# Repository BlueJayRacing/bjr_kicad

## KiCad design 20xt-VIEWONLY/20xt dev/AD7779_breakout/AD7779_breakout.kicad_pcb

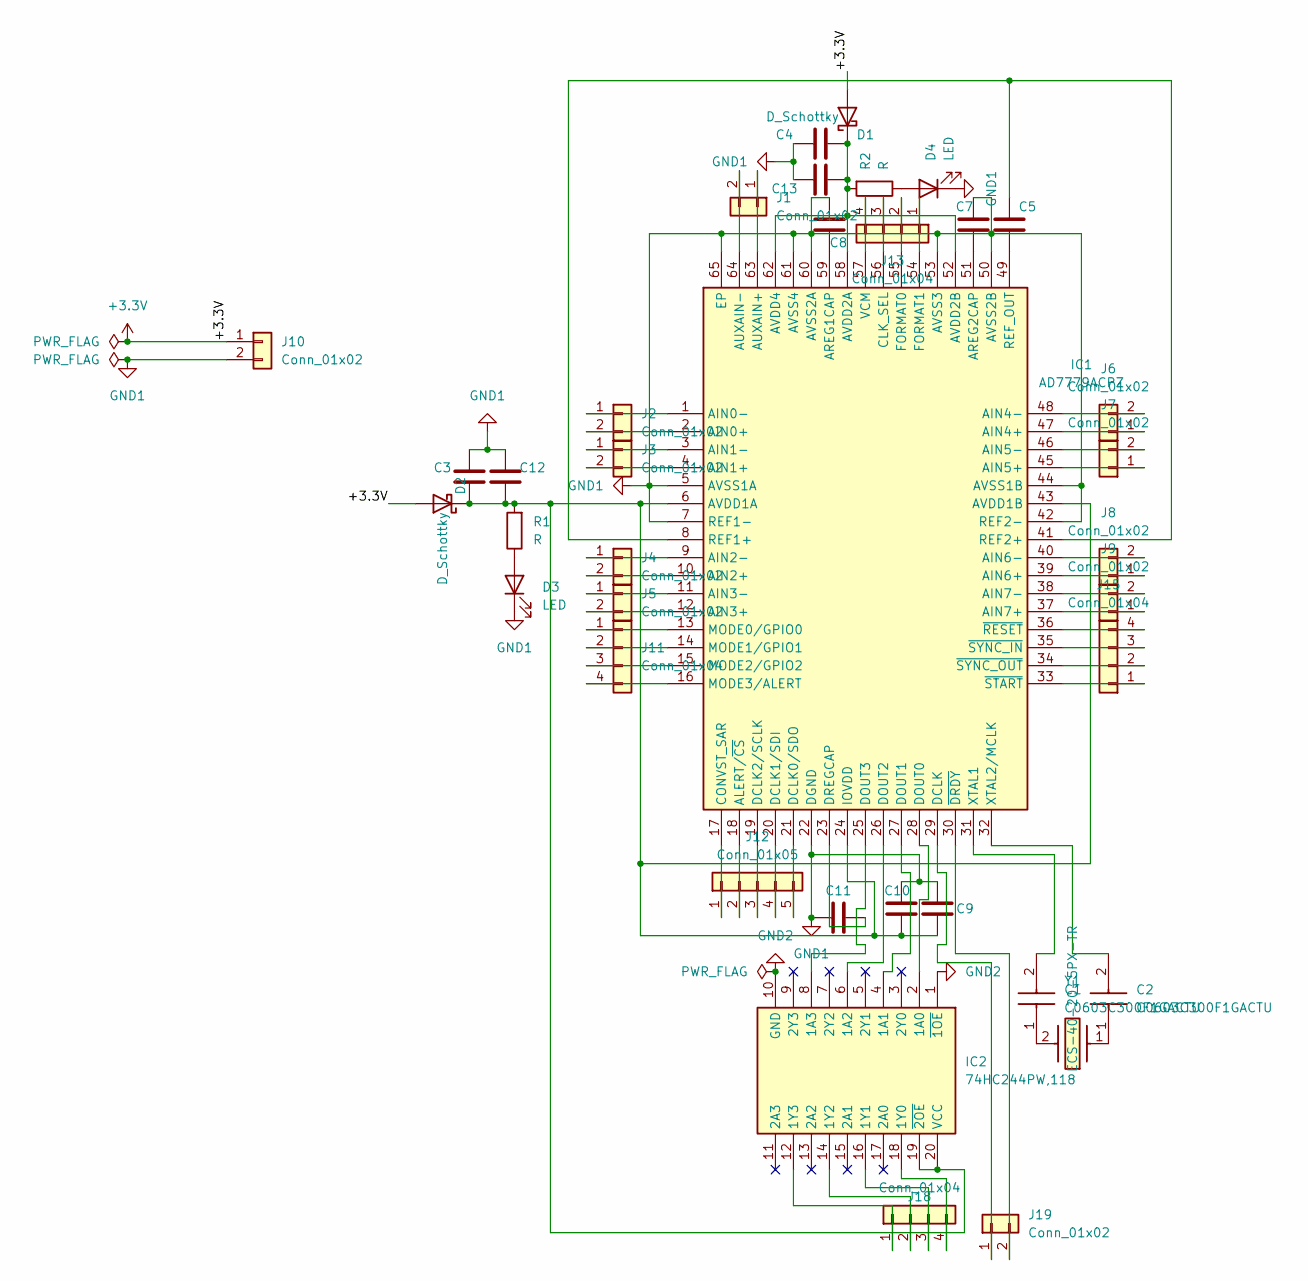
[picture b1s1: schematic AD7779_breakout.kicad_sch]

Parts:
C1, C2: C0603C300F1GACTU; C_01005_0402Metric; Mouser Part Number 80-C0603C300F1GACTU
C3, C4, C5, C9: C; CAPC1608X95N
C7, C8, C11: C; CAPC1005X55N
C10: C; C_0805_2012Metric_Pad1.18x1.45mm_HandSolder
C12: C; CAPC2012X94N
C13: C; C_0805_2012Metric
D1, D2: D_Schottky; DIOM5336X245N
D3, D4: LED; LED_0201_0603Metric
IC1: AD7779ACPZ; QFN50P900X900X80-65N-D; Mouser Part Number 584-AD7779ACPZ
IC2: 74HC244PW,118; SOP65P640X110-20N; Mouser Part Number 771-74HC244PW-T
J1, J2, J3, J4, J5, J6, J7, J8, J9, J10, J19: Conn_01x02; PinHeader_1x02_P2.54mm_Vertical
J11, J13, J15, J18: Conn_01x04; PinHeader_1x04_P2.54mm_Vertical
J12: Conn_01x05; PinHeader_1x05_P2.54mm_Vertical
R1, R2: R; R_0603_1608Metric
Y1: ECS-40-20-5PX-TR; ECS49205PXTR; Mouser Part Number 520-CSM400-20-X

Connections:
+3.3V: D1.2 (A), D2.2 (A), J10.1
GND1: C3.1, C4.1, C7.1, C8.1, C9.2, C10.2, C11.2, C12.1, C13.1, D3.1 (K), D4.1 (K), IC1.5 (AVSS1A), IC1.7 (REF1-), IC1.22 (DGND), IC1.42 (REF2-), IC1.44 (AVSS1B), IC1.50 (AVSS2B), IC1.53 (AVSS3), IC1.60 (AVSS2A), IC1.61 (AVSS4), IC1.65 (EP), J10.2
GND2: IC2.1 (~1OE), IC2.10 (GND)
unnamed: C1.1, Y1.2
unnamed: C2.1, Y1.1
unnamed: C4.2, C13.2, D1.1 (K), IC1.52 (AVDD2B), IC1.58 (AVDD2A), IC1.62 (AVDD4), R2.2
unnamed: C3.2, C9.1, C10.1, C12.2, D2.1 (K), IC1.6 (AVDD1A), IC1.24 (IOVDD), IC1.43 (AVDD1B), IC2.19 (~2OE), IC2.20 (VCC), R1.2
unnamed: D3.2 (A), R1.1
unnamed: D4.2 (A), R2.1
unnamed: IC1.2 (AIN0+), J2.2
unnamed: IC1.1 (AIN0-), J2.1
unnamed: IC1.4 (AIN1+), J3.2
unnamed: IC1.3 (AIN1-), J3.1
unnamed: IC1.10 (AIN2+), J4.2
unnamed: IC1.9 (AIN2-), J4.1
unnamed: IC1.12 (AIN3+), J5.2
unnamed: IC1.11 (AIN3-), J5.1
unnamed: IC1.47 (AIN4+), J6.1
unnamed: IC1.48 (AIN4-), J6.2
unnamed: IC1.45 (AIN5+), J7.1
unnamed: IC1.46 (AIN5-), J7.2
unnamed: IC1.39 (AIN6+), J8.1
unnamed: IC1.40 (AIN6-), J8.2
unnamed: IC1.37 (AIN7+), J9.1
unnamed: IC1.38 (AIN7-), J9.2
unnamed: IC1.18 (ALERT/~CS), J12.2
unnamed: C8.2, IC1.59 (AREG1CAP)
unnamed: C7.2, IC1.51 (AREG2CAP)
unnamed: IC1.63 (AUXAIN+), J1.1
unnamed: IC1.64 (AUXAIN-), J1.2
unnamed: IC1.56 (CLK_SEL), J13.3
unnamed: IC1.17 (CONVST_SAR), J12.1
unnamed: IC1.21 (DCLK0/SDO), J12.5
unnamed: IC1.20 (DCLK1/SDI), J12.4
unnamed: IC1.19 (DCLK2/SCLK), J12.3
unnamed: IC1.29 (DCLK), J19.1
unnamed: IC1.28 (DOUT0), IC2.2 (1A0)
unnamed: IC1.27 (DOUT1), IC2.4 (1A1)
unnamed: IC1.26 (DOUT2), IC2.6 (1A2)
unnamed: IC1.25 (DOUT3), IC2.8 (1A3)
unnamed: C11.1, IC1.23 (DREGCAP)
unnamed: IC1.55 (FORMAT0), J13.2
unnamed: IC1.54 (FORMAT1), J13.1
unnamed: IC1.13 (MODE0/GPIO0), J11.1
unnamed: IC1.14 (MODE1/GPIO1), J11.2
unnamed: IC1.15 (MODE2/GPIO2), J11.3
unnamed: IC1.16 (MODE3/ALERT), J11.4
unnamed: C5.1, IC1.8 (REF1+), IC1.41 (REF2+)
unnamed: C5.2, IC1.49 (REF_OUT)
unnamed: IC1.57 (VCM), J13.4
unnamed: C1.2, IC1.31 (XTAL1)
unnamed: C2.2, IC1.32 (XTAL2/MCLK)
unnamed: IC1.30 (~DRDY), J19.2
unnamed: IC1.36 (~RESET), J15.4
unnamed: IC1.33 (~START), J15.1
unnamed: IC1.35 (~SYNC_IN), J15.3
unnamed: IC1.34 (~SYNC_OUT), J15.2
unnamed: IC2.18 (1Y0), J18.4
unnamed: IC2.16 (1Y1), J18.3
unnamed: IC2.14 (1Y2), J18.2
unnamed: IC2.12 (1Y3), J18.1

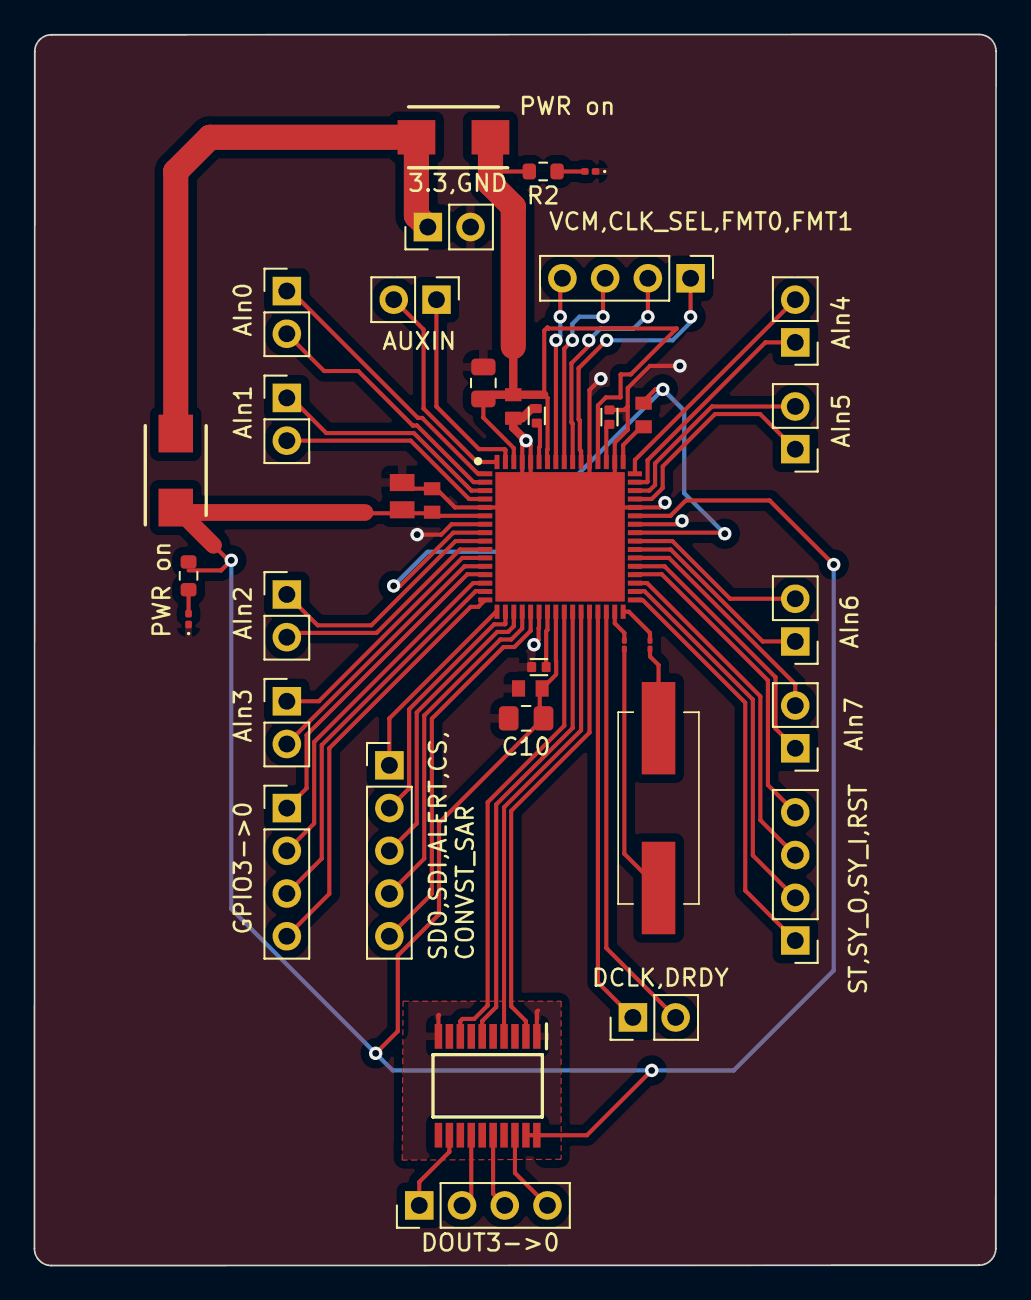
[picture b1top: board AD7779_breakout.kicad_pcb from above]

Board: 2 copper layers, 57.2 x 73.2 mm, 37 parts (0 on the bottom side), 61 nets.

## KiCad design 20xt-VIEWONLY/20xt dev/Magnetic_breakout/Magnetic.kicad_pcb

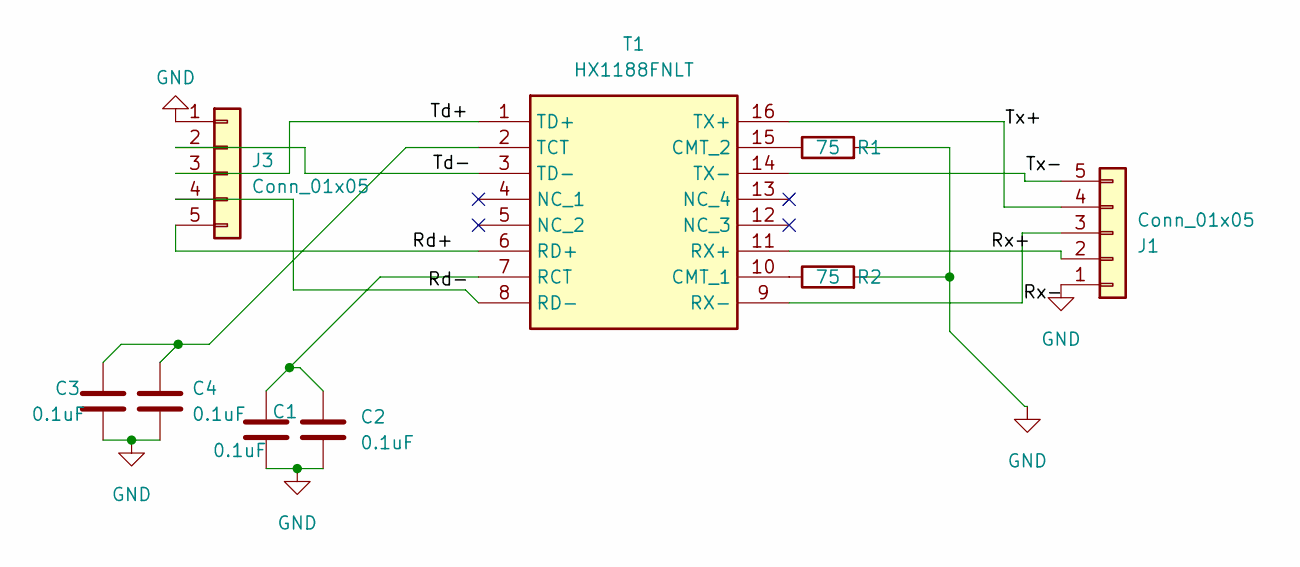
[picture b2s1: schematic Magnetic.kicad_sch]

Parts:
C1, C2, C3, C4: 0.1uF; C_0603_1608Metric
J1, J3: Conn_01x05; Molex_PicoBlade_53047-0510_1x05_P1.25mm_Vertical
R1, R2: 75; R_0603_1608Metric
T1: HX1188FNLT; Mouser Part Number 673-HX1188FNLT

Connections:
/Rd+: J3.5, T1.6 (RD+)
/Rd-: J3.4, T1.8 (RD-)
/Rx+: J1.2, T1.11 (RX+)
/Rx-: J1.3, T1.9 (RX-)
/Td+: J3.3, T1.1 (TD+)
/Td-: J3.2, T1.3 (TD-)
/Tx+: J1.4, T1.16 (TX+)
/Tx-: J1.5, T1.14 (TX-)
GND: C1.2, C2.2, C3.2, C4.2, J1.1, J3.1, R1.2, R2.2
unnamed: R2.1, T1.10 (CMT_1)
unnamed: R1.1, T1.15 (CMT_2)
unnamed: C1.1, C2.1, T1.7 (RCT)
unnamed: C3.1, C4.1, T1.2 (TCT)

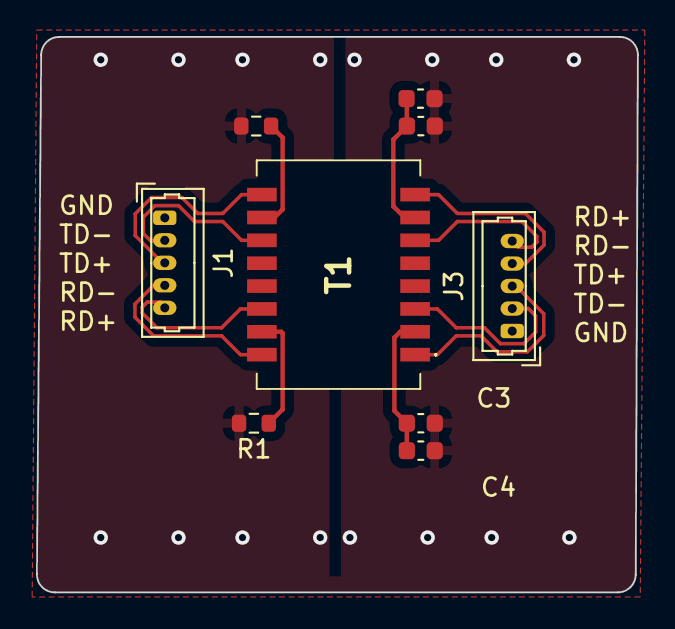
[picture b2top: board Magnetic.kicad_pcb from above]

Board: 2 copper layers, 33.4 x 30.9 mm, 9 parts (0 on the bottom side), 13 nets.

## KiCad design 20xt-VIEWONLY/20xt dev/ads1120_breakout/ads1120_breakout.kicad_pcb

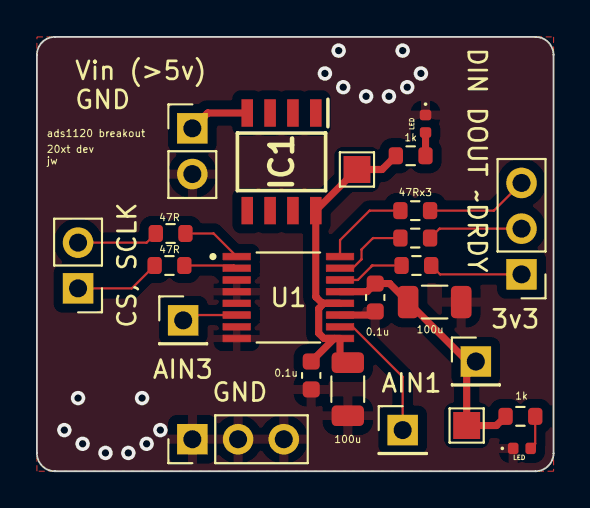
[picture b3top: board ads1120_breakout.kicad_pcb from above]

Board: 2 copper layers, 28.7 x 24.1 mm, 24 parts (0 on the bottom side), 18 nets.

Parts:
C1, C4: 100u; C_1206_3216Metric
C2, C3: 0.1u; C_0603_1608Metric
D1, D2: LED; D_0402_1005Metric
IC1: LT1009S8#PBF; SOIC127P599X175-8N
J1, J2: Conn_01x02; PinHeader_1x02_P2.54mm_Vertical
J3, J4, J6: Conn_01x01; PinHeader_1x01_P2.54mm_Vertical
J5, J7: Conn_01x03; PinHeader_1x03_P2.54mm_Vertical
R1, R2, R3, R4, R5: 47; R_0603_1608Metric
R6, R7: 1k; R_0603_1608Metric
TP1, TP2: TestPoint; TestPoint_Pad_1.5x1.5mm
U1: ADS1120IPWR; SOP65P640X120-16N

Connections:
2.5v: C1.1, C2.2, IC1.8 ((+)_2), R7.1, TP2.1, U1.9 (REFP0), U1.12 (AVDD)
3v3: C3.2, C4.1, J6.1, R6.1, TP1.1, U1.13 (DVDD)
DIN: J5.3, R2.1
GND: C1.2, C2.1, C3.1, C4.2, D1.1 (K), D2.1 (K), J2.2, J7.1, J7.2, J7.3, U1.3 (CLK), U1.4 (DGND), U1.5 (AVSS), U1.7 (AIN2), U1.8 (REFN0), U1.11 (AIN0/REFP1)
unnamed: D1.2 (A), R6.2
unnamed: D2.2 (A), R7.2
unnamed: J1.1, R1.1
unnamed: J1.2, R3.1
unnamed: J3.1, U1.10 (AIN1)
unnamed: J4.1, U1.6 (AIN3/REFN1)
unnamed: J5.1, R4.1
unnamed: J5.2, R5.2
unnamed: R2.2, U1.16 (DIN)
unnamed: R5.1, U1.15 (DOUT/~DRDY)
unnamed: R3.2, U1.1 (SCLK)
unnamed: R1.2, U1.2 (~CS)
unnamed: R4.2, U1.14 (~DRDY)
Vin: IC1.4 ((-)), J2.1

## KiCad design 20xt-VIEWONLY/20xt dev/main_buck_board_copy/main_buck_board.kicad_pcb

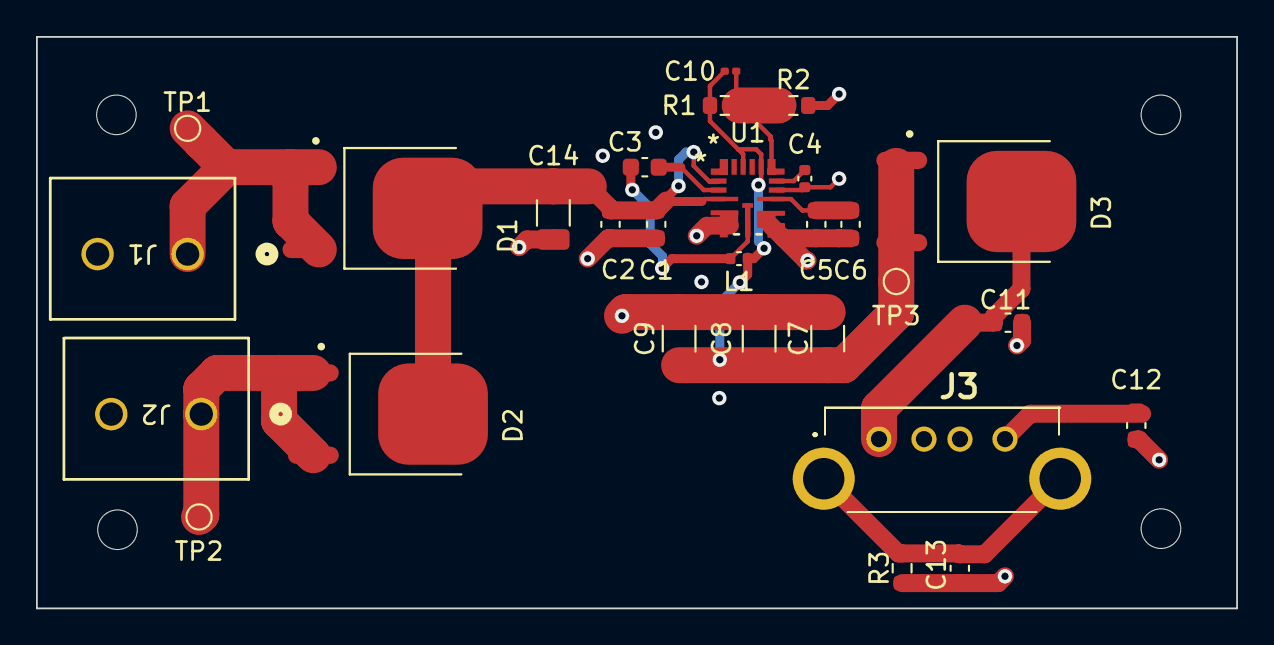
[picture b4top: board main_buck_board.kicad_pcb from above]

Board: 4 copper layers, 66.7 x 31.8 mm, 32 parts (0 on the bottom side), 13 nets.

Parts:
C1, C3, C5, C11, C12, C13: 0.1uF; C_0603_1608Metric
C2, C6: 10uF; C_0603_1608Metric
C4: 2.2uF; C_0402_1005Metric
C7, C8, C9, C14: 100uF; C_1206_3216Metric
C10: 56pF; C_0201_0603Metric
D1, D2, D3: D_Schottky_AKA; DPAK228P990X239-4N
H1, H2, H3, H4: MountingHole; MountingHole_2.2mm_M2
J1, J2: 691137710002; CONN2_710002_WRE
J3: UJ2-AV-4-TH; UJ2AV4TH
L1: 2.2uH; C_0402_1005Metric
R1: 51.1k; R_0603_1608Metric
R2: 10k; R_0603_1608Metric
R3: 100k; R_0603_1608Metric
TP1, TP2, TP3: TestPoint; TestPoint_Pad_D1.0mm
U1: 21-100700_90-100240_ADI

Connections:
GND: C1.2, C2.2, C4.2, C5.2, C6.2, C7.1, C8.1, C9.1, C11.2, C12.1, C13.2, C14.2, J1.2, J2.2, R2.2, R3.2, U1.4 (PGND), U1.5 (PGND), U1.7 (PGND), U1.8 (PGND), U1.10 (GND)
unnamed: C5.1, C6.1, U1.9 (SUP)
unnamed: C12.2, J3.4
unnamed: C13.1, J3.MH1, J3.MH2, R3.1
unnamed: D1.1 (A), D1.3 (A), J1.1, TP1.1
unnamed: C1.1, C2.1, C14.1, D1.2 (K), D2.2 (K), U1.1 (EN), U1.3 (SUP)
unnamed: D2.1 (A), D2.3 (A), J2.1, TP2.1
unnamed: C11.1, D3.2 (K), J3.1
unnamed: C4.1, U1.11 (BIAS)
unnamed: C3.1, U1.2 (BST)
unnamed: C10.2, R1.2, R2.1, U1.12 (FB)
unnamed: C3.2, L1.1, U1.6 (LX)
unnamed: C7.2, C8.2, C9.2, C10.1, D3.1 (A), D3.3 (A), L1.2, R1.1, TP3.1, U1.13 (OUT), U1.15 (PGOOD)

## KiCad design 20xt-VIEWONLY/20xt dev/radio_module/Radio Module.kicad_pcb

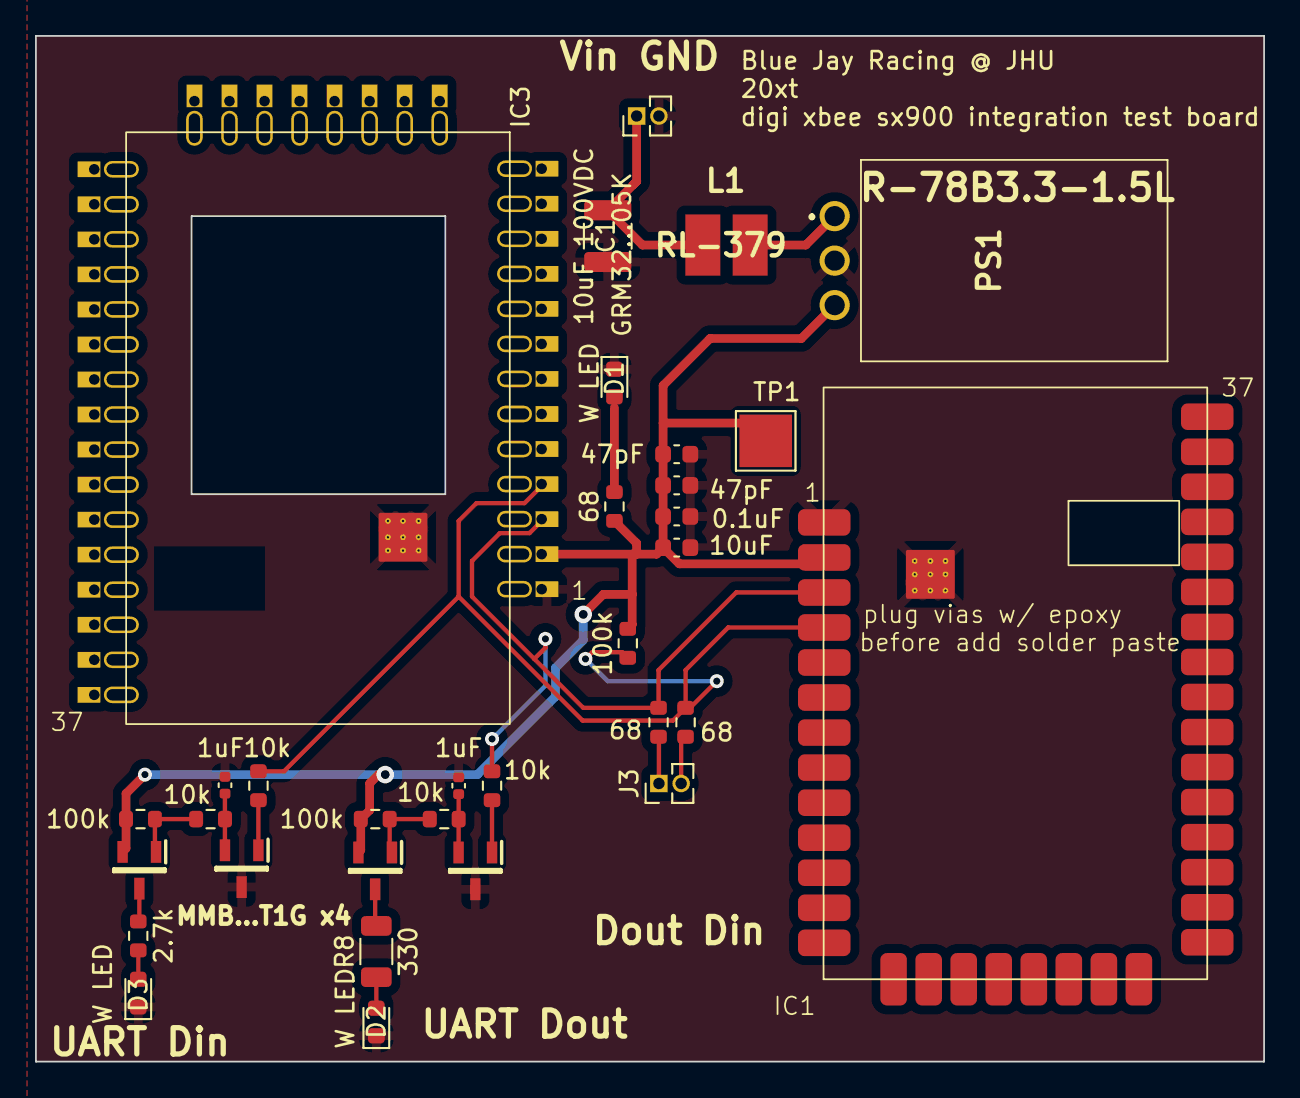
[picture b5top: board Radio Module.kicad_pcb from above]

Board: 2 copper layers, 70.1 x 58.5 mm, 33 parts (0 on the bottom side), 19 nets.

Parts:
C1: 10uF 100VDC; C_1210_3225Metric
C2: 10uF; C_0603_1608Metric
C3: 0.1uF; C_0603_1608Metric
C4, C5: 47pF; C_0603_1608Metric
C6, C7: 1uF; C_0402_1005Metric
D1, D3: W LED; LED_0603_1608Metric
D2: LED; LED_0603_1608Metric
IC1: XBP9X-DMUS-011; xbee sx 900
IC3: XBP9X-DMUS-011; xbee sx 900 flexy
IC4, IC5, IC6, IC7: MMBT3906LT1G; SOT96P237X111-3N
J3, J4: Conn_01x02; PinHeader_1x02_P1.27mm_Vertical
L1: 3.9uH; RLS397
PS1: R-78B3.3-1.5L; R78B5015L
R1, R2, R3: 68; R_0603_1608Metric
R4, R7, R11: 100k; R_0603_1608Metric
R5, R6, R9, R10: 10k; R_0603_1608Metric
R8: 330; R_1206_3216Metric
R12: 2.7k; R_0603_1608Metric
TP1: TestPoint; TestPoint_Pad_3.0x3.0mm

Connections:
Din: IC1.4 (DIN/DIO14/~CONFIG), IC3.4 (DIN/DIO14/~CONFIG), R1.2, R4.2, R10.1
Dout: IC1.3 (DIO13/DOUT), IC3.3 (DIO13/DOUT), R2.2, R5.1
GND: C1.2, C2.1, C3.1, C4.1, C5.1, C6.2, C7.2, D1.1 (K), D2.1 (K), D3.1 (K), IC1.1 (GND_1), IC1.38 (GND_6), IC3.1 (GND_1), IC3.38 (GND_6), IC4.3 (C), IC6.3 (C), J4.2, PS1.2 (GND)
unnamed: D1.2 (A), R3.1
unnamed: D2.2 (A), R8.1
unnamed: D3.2 (A), R12.1
unnamed: IC4.1 (B), R5.2
unnamed: C6.1, IC4.2 (E), R6.1
unnamed: IC5.1 (B), R6.2, R7.2
unnamed: IC5.3 (C), R8.2
unnamed: IC6.1 (B), R10.2
unnamed: C7.1, IC6.2 (E), R9.1
unnamed: IC7.1 (B), R9.2, R11.2
unnamed: IC7.3 (C), R12.2
unnamed: J3.1, R2.1
unnamed: J3.2, R1.1
unnamed: L1.2, PS1.1 (+VIN)
Vcc: C2.2, C3.2, C4.2, C5.2, IC1.2 (VCC), IC3.2 (VCC), IC5.2 (E), IC7.2 (E), PS1.3 (+VOUT), R3.2, R4.1, R7.1, R11.1, TP1.1
Vin: C1.1, J4.1, L1.1

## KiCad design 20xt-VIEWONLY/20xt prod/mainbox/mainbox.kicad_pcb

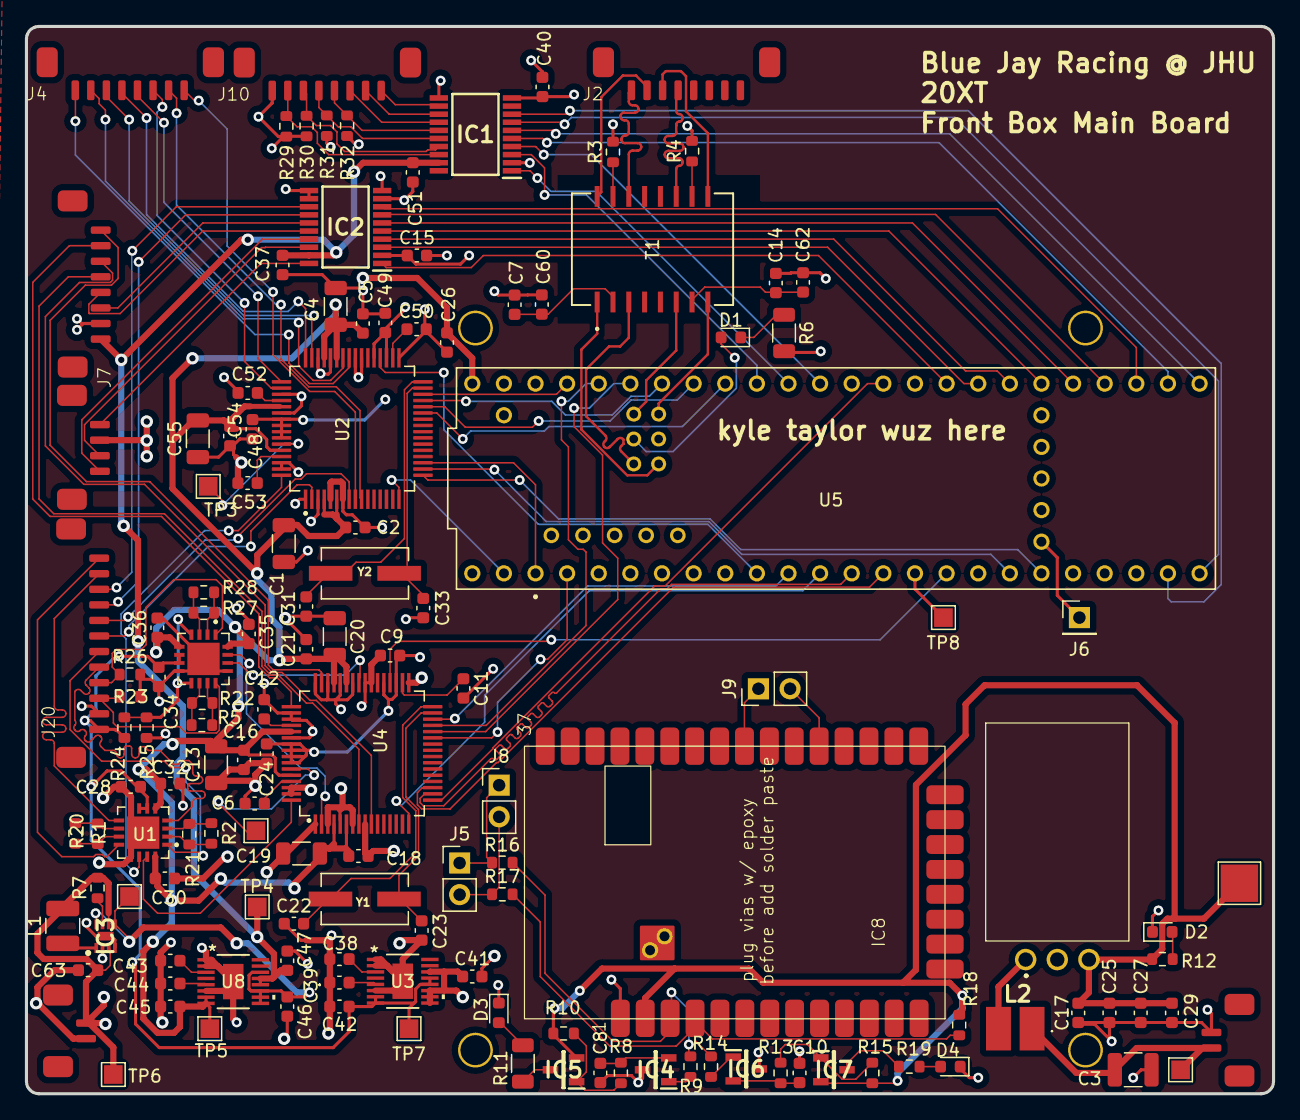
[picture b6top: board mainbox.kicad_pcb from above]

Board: 4 copper layers, 100.2 x 85.7 mm, 141 parts (0 on the bottom side), 139 nets.

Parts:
C1, C4, C13, C19, C20, C55: 100uF; C_1206_3216Metric
C2, C5, C9, C15, C16, C18, C21, C24, C25, C26, C28, C30, C32, C34, C35, C36, C37, C39, C40, C41, C44, C46, C48, C49, C51, C54, C60, C62: 0.1uF; C_0603_1608Metric
C3: 10uF 100VDC; C_1210_3225Metric
C6, C7, C8, C10, C11, C12, C14, C38, C42, C43, C45, C47, C50, C52, C53: 1uF; C_0603_1608Metric
C17: 10uF; C_0603_1608Metric
C22, C23, C31, C33: 35pF; C_0603_1608Metric
C27, C29: 47pF; C_0603_1608Metric
C63: 4.7uF; C_0603_1608Metric
D1, D2, D3, D4: LED; LED_0603_1608Metric
H1, H2, H3, H4: MountingHole; 2.35mm_mounting_hole
IC1, IC2: TXB0108PWR; SOP65P640X120-20N
IC3: MIC2876-5.5YMT-TR; SON50P200X200X60-9N-D
IC4, IC5, IC6, IC7: MMBT3906LT1G; SOT96P237X111-3N
IC8: XBP9X-DMUS-011; xbee sx 900
J1: Conn_01x04; SMD_picoblade_hori_1x04
J2, J4, J7, J10: Conn_01x08; SMD_picoblade_hori_1x08
J3, J21: Conn_01x02; SMD_picoblade_hori_1x02
J5, J8, J9: Conn_01x02; PinHeader_1x02_P2.54mm_Vertical
J6: Conn_01x01; PinHeader_1x01_P2.54mm_Vertical
J20: Conn_01x12; SMD_picoblade_hori_1x12
L1: 1uH; L_1210_3225Metric
L2: 3.9uH; RLS397
PS1: R-78B3.3-1.5L; R78B5015L
R1, R2, R5, R20, R21, R22, R27, R28: 47; R_0603_1608Metric
R3, R4: 75; R_0603_1608Metric
R6, R11: 330; R_1206_3216Metric
R7: 1M; R_0603_1608Metric
R8, R9, R13, R14: 10k; R_0603_1608Metric
R10, R15, R18, R29, R30, R31, R32: 100k; R_0603_1608Metric
R12, R16, R17: 68; R_0603_1608Metric
R19: 2.7k; R_0603_1608Metric
R23, R24, R25, R26: 120; R_0603_1608Metric
T1: 2337822-1; CONN16_2337822-1_TEC
TP1, TP2, TP3, TP4, TP5, TP6, TP7, TP8, TP10: TestPoint; TestPoint_Pad_1.5x1.5mm
TP9: TestPoint; TestPoint_Pad_3.0x3.0mm
U1, U6: AD8222ACPZ-R7; QFN65P400X400X80-17N
U2, U4: AD7768BSTZ; QFP50P1200X1200X160-64N
U3: LT6658AHMSE-2.5-PBF; MSE_16_ADI
U5: DEV-16771; MODULE_DEV-16771
U8: LT6658AHMSE-5-PBF; MSE_16_ADI
Y1, Y2: ECS-160-20-3X-TR; XTAL_ECS-160-20-3X-TR

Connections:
2.5vsg: C28.1, C34.1, C42.1, J20.12, R24.1, TP7.1, U1.6 (REF1), U1.7 (REF2), U3.7 (VOUT2_S), U3.8 (VOUT2_F), U3.12 (VOUT1_F), U3.13 (VOUT1_S), U6.6 (REF1), U6.7 (REF2)
3v3: C9.1, C15.1, C24.1, C40.1, C48.1, C49.1, IC1.2 (VCCA), IC1.10 (OE), IC2.2 (VCCA), IC2.10 (OE), TP8.1, U2.35 (IOVDD), U2.37 (~START), U2.55 (FORMAT1), U2.56 (FORMAT0), U2.57 (~PIN/SPI), U2.58 (CLK_SEL), U4.35 (IOVDD), U4.37 (~START), U4.55 (FORMAT1), U4.56 (FORMAT0), U4.57 (~PIN/SPI), U4.58 (CLK_SEL), U5.3.3V_1 (3.3V)
5.2v: C46.1, IC3.5 (OUTS), IC3.8 (OUT), TP2.1, U8.9 (*OD), U8.10 (VIN2), U8.11 (VIN1), U8.14 (VIN)
5vadc: C1.2, C2.1, C4.2, C5.1, C13.2, C16.1, C18.1, C19.2, C20.2, C21.1, C30.1, C32.1, C35.1, C36.1, C45.1, C54.1, C55.2, TP5.1, U1.5 (+VS), U1.16 (+VS__1), U2.4 (AVDD1A), U2.6 (REF1+), U2.43 (REF2+), U2.45 (AVDD1B), U2.53 (AVDD2B), U2.60 (AVDD2A), U4.4 (AVDD1A), U4.6 (REF1+), U4.43 (REF2+), U4.45 (AVDD1B), U4.53 (AVDD2B), U4.60 (AVDD2A), U6.5 (+VS), U6.16 (+VS__1), U8.7 (VOUT2_S), U8.8 (VOUT2_F)
5vanalog: C37.1, C47.1, C51.1, IC1.19 (VCCB), IC2.19 (VCCB), J7.8, TP4.1, U8.12 (VOUT1_F), U8.13 (VOUT1_S)
5vin: C26.1, C41.1, C63.2, IC3.3 (IN), IC3.6 (EN), J1.2, J21.1, L1.2, R7.2, TP6.1, U3.9 (*OD), U3.10 (VIN2), U3.11 (VIN1), U3.14 (VIN), U5.VIN
5vradio: C3.1, J3.1, L2.1, TP10.1
!CS1: U4.16 (ST0/~CS), U5.10 (CS1)
!CS2: U2.16 (ST0/~CS), U5.0 (RX1)
/teensy/Rx+: J2.5, T1.11 (RX+)
/teensy/Rx-: J2.6, T1.9 (RX-)
/teensy/Tx+: J2.7, T1.16 (TX+)
/teensy/Tx-: J2.8, T1.14 (TX-)
Din: IC8.4 (DIN/DIO14/~CONFIG), R14.1, R17.2, R18.2
Dout: IC8.3 (DIO13/DOUT), R9.1, R16.2
GND: C1.1, C2.2, C3.2, C4.1, C5.2, C6.2, C7.1, C8.2, C9.2, C10.2, C11.2, C12.2, C13.1, C14.1, C15.2, C16.2, C17.1, C18.2, C19.1, C20.1, C21.2, C22.1, C23.1, C24.2, C25.1, C26.2, C27.1, C28.2, C29.1, C30.2, C31.1, C32.2, C33.1, C34.2, C35.2, C36.2, C37.2, C38.2, C39.2, C40.2, C41.2, C42.2, C43.2, C44.2, C45.2, C46.2, C47.2, C48.2, C49.2, C50.2, C51.2, C52.2, C53.2, C54.2, C55.1, C60.2, C62.2, C63.1, D2.1 (K), D3.1 (K), D4.1 (K), IC1.11 (GND), IC2.9 (A8), IC2.11 (GND), IC2.12 (B8), IC3.2 (PGND), IC3.4 (AGND), IC3.9 (EP), IC4.3 (C), IC6.3 (C), IC8.1 (GND_1), IC8.38 (GND_6), J3.2, J7.7, J10.8, J20.11, J21.2, PS1.2 (GND), R3.2, R4.2, R6.2, R23.2, R25.2, R26.2, R29.1, R30.1, R31.1, R32.1, U1.8 (-VS__1), U1.13 (-VS), U1.17 (EP), U2.1 (AIN1-), U2.3 (AVSS1A), U2.5 (REF1-), U2.7 (AIN2-), U2.33 (DGND), U2.39 (AIN7+), U2.40 (AIN7-), U2.44 (REF2-), U2.46 (AVSS1B), U2.51 (AVSS2B), U2.54 (AVSS), U2.62 (AVSS2A), U2.63 (AIN0-), U3.1 (GND), U3.2 (GND), U3.6 (GND), U3.EPAD, U4.1 (AIN1-), U4.3 (AVSS1A), U4.5 (REF1-), U4.7 (AIN2-), U4.9 (AIN3-), U4.33 (DGND), U4.39 (AIN7+), U4.40 (AIN7-), U4.42 (AIN6-), U4.44 (REF2-), U4.46 (AVSS1B), U4.48 (AIN5-), U4.50 (AIN4-), U4.51 (AVSS2B), U4.54 (AVSS), U4.62 (AVSS2A), U4.63 (AIN0-), U5.GND1 (GND), U5.GND2 (GND__1), U5.GND3 (GND__2), U5.GND4 (GND__3), U5.GND5 (GND__4), U5.USB_GND1 (USB_GND), U5.USB_GND2 (USB_GND__1), U6.8 (-VS__1), U6.13 (-VS), U6.17 (EP), U8.1 (GND), U8.2 (GND), U8.6 (GND), U8.EPAD
unnamed: D1.2 (A), U5.LED
unnamed: D1.1 (K), R6.1
unnamed: D2.2 (A), R12.1
unnamed: D3.2 (A), R11.1
unnamed: D4.2 (A), R19.1
unnamed: IC2.1 (A1), U5.41 (A17)
unnamed: IC2.3 (A2), U5.40 (A16)
unnamed: IC2.4 (A3), U5.39 (A15)
unnamed: IC2.5 (A4), U5.38 (A14)
unnamed: IC2.6 (A5), U5.37 (CS3)
unnamed: IC2.7 (A6), U5.36 (CS2)
unnamed: IC2.8 (A7), U5.35 (TX8)
unnamed: IC3.1 (SW), L1.1
unnamed: IC3.7 (/PG), R7.1
unnamed: IC4.1 (B), R9.2
unnamed: C8.1, IC4.2 (E), R8.1
unnamed: IC5.1 (B), R8.2, R10.2
unnamed: IC5.3 (C), R11.2
unnamed: IC6.1 (B), R14.2
unnamed: C10.1, IC6.2 (E), R13.1
unnamed: IC7.1 (B), R13.2, R15.2
unnamed: IC7.3 (C), R19.2
unnamed: IC8.29 (DIO6/~RTS), J9.1
unnamed: IC8.26 (DIO9/ON/~SLEEP), J9.2
unnamed: J4.1, U2.9 (AIN3-)
unnamed: J4.2, U2.10 (AIN3+)
unnamed: J4.3, U2.50 (AIN4-)
unnamed: J4.4, U2.49 (AIN4+)
unnamed: J4.5, U2.48 (AIN5-)
unnamed: J4.6, U2.47 (AIN5+)
unnamed: J4.7, U2.42 (AIN6-)
unnamed: J4.8, U2.41 (AIN6+)
unnamed: J5.1, J8.1, R16.1
unnamed: J5.2, J8.2, R17.1
unnamed: J6.1, U5.VBAT
unnamed: J20.1, U1.12 (-IN2)
unnamed: J20.2, U1.9 (+IN2)
unnamed: J20.7, U1.1 (-IN1)
unnamed: J20.8, U1.4 (+IN1)
unnamed: L2.2, PS1.1 (+VIN)
unnamed: R4.1, T1.10 (CMT_1)
unnamed: R3.1, T1.15 (CMT_2)
unnamed: C14.2, C62.1, T1.7 (RCT)
unnamed: C7.2, C60.1, T1.2 (TCT)
unnamed: R2.1, R21.1, U1.2 (RG1)
unnamed: R2.2, R21.2, U1.3 (RG1__1)
unnamed: R1.1, R20.1, U1.10 (RG2)
unnamed: R1.2, R20.2, U1.11 (RG2__1)
unnamed: C50.1, U2.34 (DREGCAP)
unnamed: C53.1, U2.61 (REGCAPA)
unnamed: C52.1, U2.52 (REGCAPB)
unnamed: TP3.1, U2.59 (VCM)
unnamed: C38.1, U3.3 (BYPASS)
unnamed: C39.1, U3.5 (NR)
unnamed: C11.1, U4.34 (DREGCAP)
unnamed: C6.1, U4.61 (REGCAPA)
unnamed: C12.1, U4.52 (REGCAPB)
unnamed: TP1.1, U4.59 (VCM)
unnamed: R27.1, R28.1, U6.2 (RG1)
unnamed: R27.2, R28.2, U6.3 (RG1__1)
unnamed: R5.1, R22.1, U6.10 (RG2)
unnamed: R5.2, R22.2, U6.11 (RG2__1)
unnamed: C43.1, U8.3 (BYPASS)
unnamed: C44.1, U8.5 (NR)
Rd+: T1.6 (RD+), U5.R+
Rd-: T1.8 (RD-), U5.R-
S1: IC1.5 (A4), U5.34 (RX8)
S2: IC1.6 (A5), U5.33 (MCLK2)
S3: IC1.7 (A6), U5.32 (OUT1B)
S4: IC1.8 (A7), U5.31 (CTX3)
S15: IC1.15 (B5), J10.4, R32.2
S25: IC1.16 (B4), J10.5, R31.2
S35: IC1.17 (B3), J10.6, R30.2
S45: IC1.18 (B2), J10.7, R29.2
SCL: IC1.3 (A2), U5.17 (A3)
SCL5: IC1.14 (B6), J10.3
SCLK1: U4.17 (ST1/SCLK), U5.13 (SCK)
SCLK2: U2.17 (ST1/SCLK), U5.27 (A13)
SDA: IC1.1 (A1), U5.16 (A2)
SDA5: IC1.13 (B7), J10.2
SDI1: U4.18 (DEC1/SDI), U5.11 (MOSI)
SDI2: U2.18 (DEC1/SDI), U5.26 (A12)
SDO1: U4.19 (DEC0/SDO), U5.12 (MISO)
SDO2: U2.19 (DEC0/SDO), U5.1 (TX1)
Td+: T1.1 (TD+), U5.T+
Td-: T1.3 (TD-), U5.T-
Vcc: C17.2, C25.2, C27.2, C29.2, IC5.2 (E), IC7.2 (E), IC8.2 (VCC), PS1.3 (+VOUT), R10.1, R12.2, R15.1, R18.1, TP9.1
aux1.1: J20.6, U2.2 (AIN1+)
aux1.2: J20.5, U2.8 (AIN2+)
auxsg: U1.14 (OUT2), U2.64 (AIN0+)
brake1: J7.2, U4.49 (AIN4+)
brake2: J7.1, U4.47 (AIN5+)
daux1: IC2.14 (B6), J20.4
daux2: IC2.13 (B7), J20.3
dclk1: U4.28 (DCLK), U5.21 (A7)
dclk2: U2.28 (DCLK), U5.19 (A5)
dout1: U4.27 (DOUT0), U5.2 (OUT2)
dout2: U2.27 (DOUT0), U5.18 (A4)
doutlcd: IC1.4 (A3), U5.15 (A1)
doutlcd5: IC1.12 (B8), J10.1
drdy1: U4.29 (~DRDY), U5.22 (A8)
drdy2: U2.29 (~DRDY), U5.20 (A6)
enc1: IC2.17 (B3), J1.4
enc2: IC2.18 (B2), J1.3
enc3: IC2.20 (B1), J1.1
hall1: IC2.15 (B5), J7.6
hall2: IC2.16 (B4), J7.5
pots1: J7.4, U4.8 (AIN2+)
pots2: J7.3, U4.10 (AIN3+)
rst1: U4.30 (~RESET), U5.9 (OUT1C)
rst2: U2.30 (~RESET), U5.23 (A9)
steerCol: U1.15 (OUT1), U4.64 (AIN0+)
syncin1: U4.36 (~SYNC_IN), U5.24 (A10)
syncin2: U2.36 (~SYNC_IN), U5.8 (TX2)
tieRod1: U4.2 (AIN1+), U6.15 (OUT1)
tieRod2: U4.41 (AIN6+), U6.14 (OUT2)
tr1-: J20.9, R26.1, U6.1 (-IN1)
tr2-: J20.10, R23.1, U6.12 (-IN2)
tr+: R24.2, R25.1, U6.4 (+IN1), U6.9 (+IN2)
xtal1.1: C23.2, U4.31 (XTAL1), Y1.2
xtal1.2: C22.2, U4.32 (XTAL2/MCLK), Y1.1
xtal2.1: C33.2, U2.31 (XTAL1), Y2.2
xtal2.2: C31.2, U2.32 (XTAL2/MCLK), Y2.1
